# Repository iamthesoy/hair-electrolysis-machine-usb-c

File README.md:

# Hair Electrolysis Machine v4

### DIY electrolysis carries risk of permanent scarring if done improperly. If something goes wrong, only you are responsible.

---
This is a fork of zoemaestra's USB-C/STM32 fork of n3tcat's original. I've swapped a few connectors to make things sterex compatible as this is the hardware i'm used to, and uploaded some "compatible" sterex accessories for cost saving :) See zoe's readme below:

This is based on n3tcat's original design but redesigned around the STM32 to cut down the BOM and make the board single sided. Unlike v3.4, this board requires no soldering to assemble, just a 340mAh LiPo battery and a display which can just be plugged in. It is even cheaper and even easier to assemble at approximately £15/$20 per board!

You should really read the guide on how to order, assemble and use: https://imzoe.me/projects/electrolysis/electrolysis

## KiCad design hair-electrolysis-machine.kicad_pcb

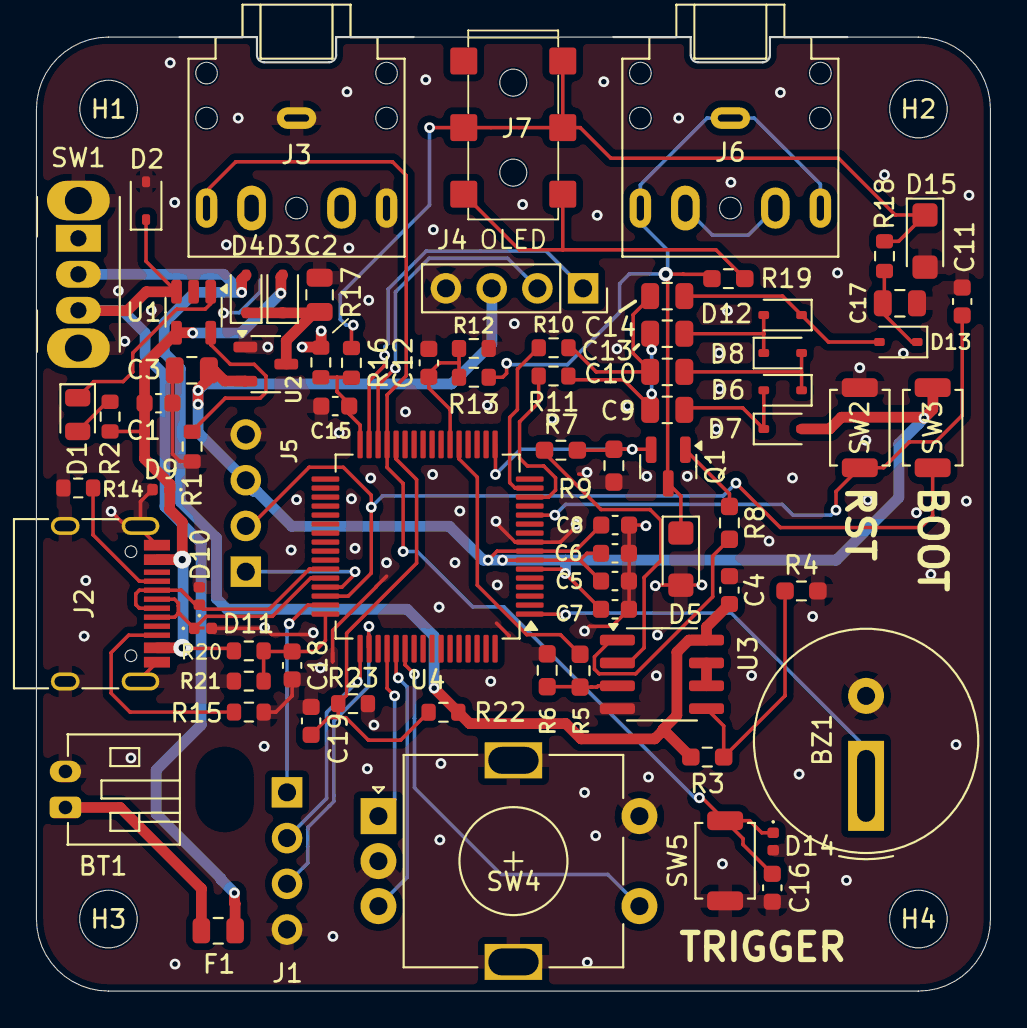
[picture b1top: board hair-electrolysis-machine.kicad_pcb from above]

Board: 2 copper layers, 53.0 x 53.0 mm, 82 parts (0 on the bottom side), 52 nets.

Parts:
BT1: Battery_Cell; JST_PH_S2B-PH-K_1x02_P2.00mm_Horizontal
BZ1: Buzzer; Buzzer_TDK_PS1240P02BT_D12.2mm_H6.5mm
C1, C5: 1uF; C_0603_1608Metric
C2, C3, C9, C10, C13, C14, C17: 4.7uF; C_0805_2012Metric
C4, C6, C7, C8, C11, C12, C15, C16, C18, C19: 100nF; C_0603_1608Metric
D1: LED; LED_0805_2012Metric
D2: 1N4148WS; D_SOD-323
D3, D4, D6, D7, D8, D12, D13: 1N5819WS; D_SOD-323
D5, D15: SMF18A; D_SMF
D9, D10, D11, D14: ESD441; D_0402_1005Metric
F1: 1A; Fuse_0805_2012Metric
H1, H2, H3, H4: MountingHole; MountingHole_3.2mm_M3
H5: MountingHole; MountingHole_2.5mm
J1: Conn_01x04_Pin; PinHeader_1x04_P2.54mm_Vertical
J2: USB_C_Receptacle_USB2.0_16P; USB_C_Receptacle_HRO_TYPE-C-31-M-12
J3, J6: AudioJack2_Ground_Switch; Jack_3.5mm_CUI_SJ1-3525N_Horizontal
J4, J5: Conn_01x04_Pin; PinSocket_1x04_P2.54mm_Vertical
J7: AudioJack2_Ground_Switch; Jack_2.5mm_PJ242_6P_12x6.2x4mm_Horizontal
Q1: BSS138; SOT-23
R1: 2.7K; R_0603_1608Metric
R2: 1K; R_0603_1608Metric
R3, R4: 100K1%; R_0603_1608Metric_Pad0.98x0.95mm_HandSolder
R5, R6, R7: 10K; R_0603_1608Metric_Pad0.98x0.95mm_HandSolder
R8, R9: 680R; R_0603_1608Metric_Pad0.98x0.95mm_HandSolder
R10, R11, R18: 100R; R_0603_1608Metric
R12, R16: 470K 1%; R_0603_1608Metric
R13, R17, R20, R21, R22, R23: 100K 1%; R_0603_1608Metric
R14, R15: 5.1K; R_0603_1608Metric
R19: 470R; R_0603_1608Metric_Pad0.98x0.95mm_HandSolder
SW1: SW_SPDT; SW_Slide_SPDT_Angled_CK_OS102011MA1Q
SW2, SW3, SW5: BTN; SW_SPST_TS-1088-xR025
SW4: RotaryEncoder_Switch; RotaryEncoder_Alps_EC11E-Switch_Vertical_H20mm
U1: TP4054; SOT-23-5
U2: XC6206PxxxMR; SOT-23-3
U3: LM358B; SOIC-8_3.9x4.9mm_P1.27mm
U4: STM32G0B1RBTx; LQFP-64_10x10mm_P0.5mm

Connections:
+3.3V: C3.1, C5.1, C6.1, C7.1, C8.1, D6.2 (A), J4.3, J5.3, SW3.2, U2.2 (VO), U4.6 (VBAT), U4.7 (VREF+), U4.8 (VDD)
+5V: C1.2, D3.2 (A), D9.1 (A1), J2.A4 (VBUS), J2.A9 (VBUS), J2.B4 (VBUS), J2.B9 (VBUS), R2.2, R20.1, U1.4 (V_{DD})
+BATT: C4.1, D4.2 (A), R3.1, R22.1, SW1.2 (B), U3.8 (V+)
/Mcu/BATT_SENSE: C19.1, R22.2, R23.1, U4.28 (PB1)
/Mcu/BODY_ELECTRODE: D15.1 (A1), J7.R, J7.S, J7.T, R16.1, R18.2
/Mcu/BTN_OK: SW4.S1, U4.54 (PD4)
/Mcu/BUZZER1: BZ1.1 (+), U4.1 (PC11)
/Mcu/D+: D11.1 (A1), J2.A6 (D+), J2.B6 (D+), U4.44 (PA10/PA12)
/Mcu/D-: D10.1 (A1), J2.A7 (D-), J2.B7 (D-), U4.43 (PA9/PA11)
/Mcu/DAC_OUT1: R5.2, U4.21 (PA4)
/Mcu/FOLLICLE_ELECTRODE: D5.1 (A1), J6.R, J6.S, J6.T, Q1.3 (D), R12.1, R19.2
/Mcu/I2C2_SCL: J4.2, U4.30 (PB10)
/Mcu/I2C2_SDA: J4.1, U4.31 (PB11)
/Mcu/OUTPUT_HIGH: C15.1, R16.2, R17.1, U4.32 (PB12)
/Mcu/OUTPUT_LOW: C12.1, R12.2, R13.1, U4.22 (PA5)
/Mcu/PA15: J1.1, U4.47 (PA15)
/Mcu/PC9: J1.2, U4.49 (PC9)
/Mcu/PD0: J1.3, U4.50 (PD0)
/Mcu/R1: SW4.B, U4.53 (PD3)
/Mcu/R2: SW4.A, U4.52 (PD2)
/Mcu/TRIGGER: C16.2, D14.1 (A1), J3.T, SW5.2, U4.29 (PB2)
/Mcu/USB_SENSE: C18.1, R20.2, R21.1, U4.48 (PC8)
/Mcu/~RESET: C11.2, SW2.1, U4.12 (PF2)
CHARGE_PUMP_OSC0: R10.1, U4.15 (PC2)
CHARGE_PUMP_OSC1: R11.1, U4.14 (PC1)
CURRENT_SENSE: Q1.2 (S), R7.2, R9.2, U4.17 (PA0)
GND: BT1.2 (-), BZ1.2 (-), C1.1, C2.2, C3.2, C4.2, C5.2, C6.2, C7.2, C8.2, C11.1, C12.2, C15.2, C16.1, C17.2, C18.2, C19.2, D2.2 (A), D5.2 (A2), D9.2 (A2), D10.2 (A2), D11.2 (A2), D14.2 (A2), D15.2 (A2), J1.4, J2.A1 (GND), J2.A12 (GND), J2.B1 (GND), J2.B12 (GND), J2.S1 (SHIELD), J3.R, J3.S, J4.4, J5.4, R1.1, R4.2, R6.1, R9.1, R13.2, R14.2, R15.2, R17.2, R21.2, R23.2, SW1.MP, SW2.2, SW4.C, SW4.MP, SW4.S2, SW5.1, U1.2 (V_{SS}), U2.1 (GND), U3.4 (V-), U4.9 (VSS)
unnamed: BT1.1 (+), F1.1
unnamed: C10.2, C14.2, R10.2
unnamed: C9.2, C13.2, R11.2
unnamed: D1.2 (A), R2.1
unnamed: D1.1 (K), U1.1 (STAT)
unnamed: D2.1 (K), F1.2, SW1.3 (C), U1.3 (V_{BAT})
unnamed: C2.1, D3.1 (K), D4.1 (K), U2.3 (VI)
unnamed: C9.1, D6.1 (K), D7.2 (A)
unnamed: C10.1, D7.1 (K), D8.2 (A)
unnamed: C13.1, D8.1 (K), D12.2 (A)
unnamed: C14.1, D12.1 (K), D13.2 (A)
unnamed: C17.1, D13.1 (K), R18.1
unnamed: J2.A5 (CC1), R14.1
unnamed: J2.B5 (CC2), R15.1
unnamed: J6.RN, J6.TN
unnamed: J7.RN, J7.TN, R19.1
unnamed: Q1.1 (G), R8.1
unnamed: R8.2, U3.1
unnamed: R1.2, U1.5 (PROG)
unnamed: R5.1, R6.2, U3.3 (+)
unnamed: R7.1, U3.2 (-)
unnamed: R3.2, R4.1, U3.5 (+)
unnamed: U3.6 (-), U3.7
SWCLK: J5.2, SW3.1, U4.46 (PA14)
SWDIO: J5.1, U4.45 (PA13)

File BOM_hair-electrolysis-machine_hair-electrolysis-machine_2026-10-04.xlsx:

No. | Quantity | Comment | Designator | Footprint | Value | Manufacturer Part | Manufacturer | Supplier Part | Supplier | LCSC
1 | 1 | HDR-M_2.54_1x1P | body | HDR-TH_1P-V-M_XKB_X4611WV-01I-C28D40
2 | 1 | Device_Battery_Cell | BT1 | Connector_JST:JST_PH_S2B-PH-K_1x02_P2.00mm_Horizontal | Battery_Cell |  |  |  |  | C16965
3 | 1 | Device_Buzzer | BZ1 | Buzzer_Beeper:Buzzer_TDK_PS1240P02BT_D12.2mm_H6.5mm | Buzzer |  |  |  |  | C76871
4 | 2 | Device_C_Small | C1,C5 | Capacitor_SMD:C_0603_1608Metric | 1uF |  |  |  |  | C15849
5 | 7 | Device_C | C2,C3,C9,C10,C13,C14,C17 | Capacitor_SMD:C_0805_2012Metric | 4.7uF |  |  |  |  | C1779
6 | 6 | Device_C_Small | C4,C6,C7,C8,C11,C16 | Capacitor_SMD:C_0603_1608Metric | 100nF |  |  |  |  | C14663
7 | 4 | Device_C | C12,C15,C18,C19 | Capacitor_SMD:C_0603_1608Metric | 100nF |  |  |  |  | C14663
8 | 1 | Device_LED | D1 | LED_SMD:LED_0805_2012Metric | LED |  |  |  |  | C84256
9 | 1 | Diode_SM4001 | D2 | Diode_SMD:D_SOD-323 | 1N4148WS |  |  |  |  | C2128
10 | 7 | Diode_1N5819WS | D3,D4,D6,D7,D8,D12,D13 | Diode_SMD:D_SOD-323 | 1N5819WS |  |  |  |  | C191023
11 | 2 | Diode_SMF18A | D5,D15 | Diode_SMD:D_SMF | SMF18A |  |  |  |  | C169433
12 | 4 | Diode_SM6T7V5A | D9,D10,D11,D14 | Diode_SMD:D_0402_1005Metric | ESD441 |  |  |  |  | C316049
13 | 1 | Device_Polyfuse | F1 | Fuse:Fuse_0805_2012Metric | 1A |  |  |  |  | C269104
14 | 4 | Mechanical_MountingHole | H1,H2,H3,H4 | MountingHole:MountingHole_3.2mm_M3 | MountingHole
15 | 1 | Mechanical_MountingHole | H5 | MountingHole:MountingHole_2.5mm | MountingHole
16 | 1 | Connector_Conn_01x04_Pin | J1 | Connector_PinHeader_2.54mm:PinHeader_1x04_P2.54mm_Vertical | Conn_01x04_Pin
17 | 1 | Connector_USB_C_Receptacle_USB2.0_16P | J2 | Connector_USB:USB_C_Receptacle_HRO_TYPE-C-31-M-12 | USB_C_Receptacle_USB2.0_16P |  |  |  |  | C165948
18 | 1 | Connector_Audio_AudioJack3_SwitchTR | J3 | Connector_Audio:Jack_3.5mm_CUI_SJ1-3525N_Horizontal | AudioJack2_Ground_Switch |  |  |  |  | C16684
19 | 2 | Connector_Conn_01x04_Pin | J4,J5 | Connector_PinSocket_2.54mm:PinSocket_1x04_P2.54mm_Vertical | Conn_01x04_Pin |  |  |  |  | C2718488
20 | 1 | 3GHz | probe | BNC-TH_DOSIN-801-0030 | 3GHz | DOSIN-801-0031 | dosinconn(德索五金) | C521205 | LCSC
21 | 1 | Transistor_FET_BSS138 | Q1 | Package_TO_SOT_SMD:SOT-23 | BSS138 |  |  |  |  | C8490
22 | 1 | Device_R | R1 | Resistor_SMD:R_0603_1608Metric | 2.7K |  |  |  |  | C13167
23 | 1 | Device_R | R2 | Resistor_SMD:R_0603_1608Metric | 1K |  |  |  |  | C21190
24 | 2 | Device_R | R3,R4 | Resistor_SMD:R_0603_1608Metric_Pad0.98x0.95mm_HandSolder | 100K1% |  |  |  |  | C25803
25 | 3 | Device_R | R5,R6,R7 | Resistor_SMD:R_0603_1608Metric_Pad0.98x0.95mm_HandSolder | 10K |  |  |  |  | C25804
26 | 2 | Device_R | R8,R9 | Resistor_SMD:R_0603_1608Metric_Pad0.98x0.95mm_HandSolder | 680R |  |  |  |  | C23228
27 | 3 | Device_R | R10,R11,R18 | Resistor_SMD:R_0603_1608Metric | 100R |  |  |  |  | C22775
28 | 2 | Device_R_Small | R12,R16 | Resistor_SMD:R_0603_1608Metric | 470K 1% |  |  |  |  | C23178
29 | 6 | Device_R_Small | R13,R17,R20,R21,R22,R23 | Resistor_SMD:R_0603_1608Metric | 100K 1% |  |  |  |  | C25803
30 | 2 | Device_R | R14,R15 | Resistor_SMD:R_0603_1608Metric | 5.1K |  |  |  |  | C23186
31 | 1 | Device_R | R19 | Resistor_SMD:R_0603_1608Metric_Pad0.98x0.95mm_HandSolder | 470R |  |  |  |  | C23179
32 | 1 | Switch_SW_SPDT | SW1 | Button_Switch_THT:SW_Slide_SPDT_Angled_CK_OS102011MA1Q | SW_SPDT |  |  |  |  | C131374
33 | 4 | Switch_SW_Push | SW2,SW3,SW5,TEST | Button_Switch_SMD:SW_SPST_TS-1088-xR025 | BTN |  |  |  |  | C720477
34 | 1 | Device_RotaryEncoder_Switch | SW4 | Rotary_Encoder:RotaryEncoder_Alps_EC11E-Switch_Vertical_H20mm | RotaryEncoder_Switch |  |  |  |  | C2991196
35 | 1 | Battery_Management_MCP73831-2-OT | U1 | Package_TO_SOT_SMD:SOT-23-5 | TP4054 |  |  |  |  | C668215
36 | 1 | Regulator_Linear_XC6206PxxxMR | U2 | Package_TO_SOT_SMD:SOT-23-3 | XC6206PxxxMR |  |  |  |  | C5446
37 | 1 | Amplifier_Operational_LM358 | U3 | Package_SO:SOIC-8_3.9x4.9mm_P1.27mm | LM358B |  |  |  |  | C1850238
38 | 1 | MCU_ST_STM32G0_STM32G0B1RBTx | U4 | Package_QFP:LQFP-64_10x10mm_P0.5mm | STM32G0B1RBTx |  |  |  |  | C5143679

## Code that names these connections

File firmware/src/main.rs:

#![no_std]
#![no_main]

mod app;
mod button;
mod buzzer;
mod charge_pump;
mod current_dac;
mod gui;
mod meter;
mod output_handler;
mod safety;
mod settings;

use core::sync::atomic::Ordering;

use app::App;
use buzzer::{BUZZER_COMMAND_CHANNEL, Buzzer};
use charge_pump::ChargePump;
use current_dac::CurrentDac;
use embassy_executor::Spawner;
use embassy_futures::select::{Either, select};
use embassy_stm32::{
    bind_interrupts, dma,
    exti::{self, ExtiInput},
    flash::Flash,
    gpio::{Input, Pull},
    i2c::{self, I2c},
    peripherals::{DMA1_CH1, DMA1_CH2, I2C2},
};
use embassy_time::Timer;
use meter::Meter;
use output_handler::OutputHandler;
use portable_atomic::AtomicI32;
use safety::USB_CONNECTED;
use settings::SettingsStore;

use defmt_rtt as _;

bind_interrupts!(struct Irqs {
    I2C2_3 => i2c::EventInterruptHandler<I2C2>, i2c::ErrorInterruptHandler<I2C2>;
    DMA1_CHANNEL1 => dma::InterruptHandler<DMA1_CH1>;
    DMA1_CHANNEL2_3 => dma::InterruptHandler<DMA1_CH2>;
    EXTI2_3 => exti::InterruptHandler<embassy_stm32::interrupt::typelevel::EXTI2_3>;
});

static ENCODER_DELTA: AtomicI32 = AtomicI32::new(0);

#[embassy_executor::task]
async fn encoder(
    mut r1: ExtiInput<'static, embassy_stm32::mode::Async>,
    mut r2: ExtiInput<'static, embassy_stm32::mode::Async>,
) {
    let mut previous = ((r1.is_high() as u8) << 1) | r2.is_high() as u8;
    let mut steps = 0i8;

    loop {
        match select(r1.wait_for_any_edge(), r2.wait_for_any_edge()).await {
            Either::First(_) | Either::Second(_) => {}
        }

        // Contact debounce settling (1 ms)
        Timer::after_millis(1).await;
        let current = ((r1.is_high() as u8) << 1) | r2.is_high() as u8;
        const STEP: [i8; 16] = [0, -1, 1, 0, 1, 0, 0, -1, -1, 0, 0, 1, 0, 1, -1, 0];
        steps += STEP[((previous << 2) | current) as usize];
        previous = current;

        if steps <= -2 {
            ENCODER_DELTA.fetch_add(1, Ordering::Relaxed);
            steps = 0;
        } else if steps >= 2 {
            ENCODER_DELTA.fetch_add(-1, Ordering::Relaxed);
            steps = 0;
        }
    }
}

#[embassy_executor::task]
async fn buzzer_handler(mut buzzer: Buzzer<'static>) {
    loop {
        buzzer.play(BUZZER_COMMAND_CHANNEL.receive().await).await;
    }
}

#[embassy_executor::task]
async fn store_handler(mut store: SettingsStore<'static>) {
    store.tick_forever().await;
}

#[embassy_executor::task]
async fn output_task(mut handler: OutputHandler<'static>) {
    handler.tick_forever().await;
}

#[embassy_executor::task]
async fn usb_monitor(input: Input<'static>) {
    let mut stable = input.is_high();
    USB_CONNECTED.store(stable, Ordering::Relaxed);
    let mut count: u8 = 0;
    loop {
        let sample = input.is_high();
        if sample != stable {
            count += 1;
            if count >= 25 {
                // 50 ms of consistent new state required to switch
                stable = sample;
                USB_CONNECTED.store(stable, Ordering::Relaxed);
                count = 0;
            }
        } else {
            count = 0;
        }
        Timer::after_millis(2).await;
    }
}

#[embassy_executor::main]
async fn main(spawner: Spawner) {
    let mut config = embassy_stm32::Config::default();
    config.rcc.pll = Some(embassy_stm32::rcc::Pll {
        source: embassy_stm32::rcc::PllSource::HSI,
        prediv: embassy_stm32::rcc::PllPreDiv::DIV1,
        mul: embassy_stm32::rcc::PllMul::MUL8,
        divp: None,
        divq: None,
        divr: Some(embassy_stm32::rcc::PllRDiv::DIV2),
    });
    config.rcc.sys = embassy_stm32::rcc::Sysclk::PLL1_R;
    let p = embassy_stm32::init(config);

    let store = SettingsStore::new(Flash::new_blocking(p.FLASH)).await;
    spawner.spawn(store_handler(store)).unwrap();

    let r2 = ExtiInput::new(p.PD2, p.EXTI2, Pull::Up, Irqs);
    let r1 = ExtiInput::new(p.PD3, p.EXTI3, Pull::Up, Irqs);
    spawner.spawn(encoder(r1, r2)).unwrap();

    spawner
        .spawn(buzzer_handler(Buzzer::new(p.TIM1, p.PC11)))
        .unwrap();

    spawner
        .spawn(usb_monitor(Input::new(p.PC8, Pull::None)))
        .unwrap();

    let meter = Meter::new(p.ADC1, p.PA0, p.PB1, p.PA5, p.PB12);
    let dac = CurrentDac::new(p.DAC1, p.PA4);
    let pump = ChargePump::new(p.TIM15, p.PC1, p.PC2);
    spawner
        .spawn(output_task(OutputHandler::new(
            pump, dac, meter, p.PB2, p.IWDG,
        )))
        .unwrap();

    let mut i2c_config = i2c::Config::default();
    i2c_config.frequency = embassy_stm32::time::Hertz(400_000);
    let display_i2c = I2c::new(
        p.I2C2, p.PB10, p.PB11, p.DMA1_CH1, p.DMA1_CH2, Irqs, i2c_config,
    );
    let mut app = App::new(display_i2c, p.PD4).await;

    loop {
        app.scroll(ENCODER_DELTA.swap(0, Ordering::Relaxed)).await;
        app.render().await;
        Timer::after_millis(5).await;
    }
}

#[panic_handler]
fn panic(_info: &core::panic::PanicInfo) -> ! {
    // Reset immediately: peripheral reset states disable TIM15 and DAC1.
    cortex_m::peripheral::SCB::sys_reset()
}

#[cortex_m_rt::exception]
unsafe fn HardFault(_frame: &cortex_m_rt::ExceptionFrame) -> ! {
    cortex_m::peripheral::SCB::sys_reset()
}
